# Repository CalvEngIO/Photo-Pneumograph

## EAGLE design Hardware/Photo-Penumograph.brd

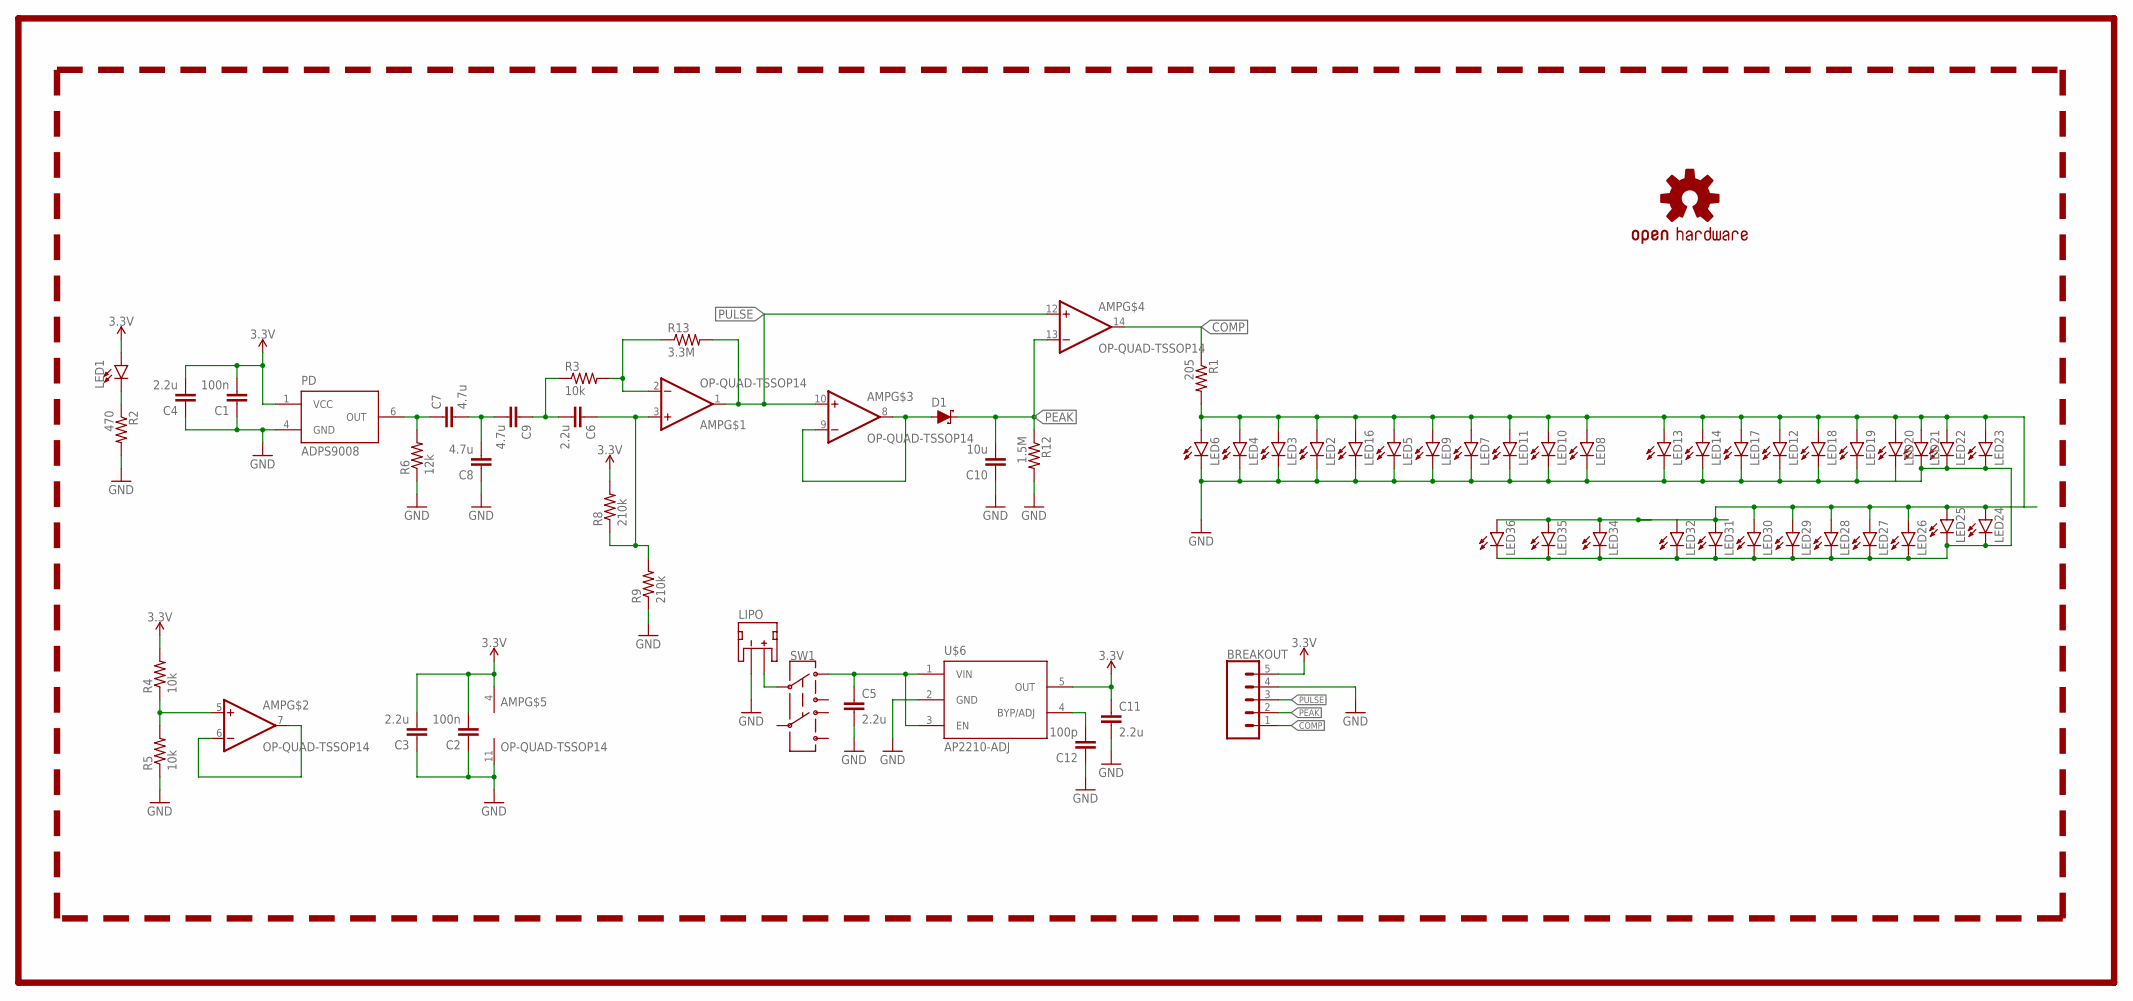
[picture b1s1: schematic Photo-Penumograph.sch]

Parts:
AMP: OP-QUAD-TSSOP14; TSSOP14
BREAKOUT: CONN_05; 1X05
C1, C2: 100n; C0402
C3, C4, C5, C6, C11: 2.2u; C0603
C7, C8, C9: 4.7u; C0603
C10: 10u; C0805
C12: 100p; C0402
D1: SCHOTTKY-SOD-123FL; SOD123
LED1: LEDZ-BEND; 2-SMD.Z-BEND
LED2, LED3, LED4, LED5, LED6, LED7, LED8, LED9, LED10, LED11, LED12, LED13, LED14, LED16, LED17, LED18, LED19, LED20, LED21, LED22, LED23, LED24, LED25, LED26, LED27, LED28, LED29, LED30, LED31, LED32, LED34, LED35, LED36: LED5MM
LIPO: JST_2MM_MALE; JST-2-SMD
LOGO1: OSHW-LOGOS; OSHW-LOGO-S
PD: ADPS9008; 6-PIN.CHIPLED
R1: 205; R0402
R2: 470; R0402
R3, R4, R5: 10k; R0402
R6: 12k; R0402
R8, R9: 210k; R0402
R12: 1.5M; R0402
R13: 3.3M; R0402
SW1: SWITCH.JS202011JCQN; SWITCH.00
U$6: AP2210-ADJ; SOT23-5

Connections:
3.3V: AMP.4 (V+), BREAKOUT.5, C1.2, C2.2, C3.2, C4.2, C11.1, LED1.+ (A), PD.1 (VCC), R4.2, R8.2, U$6.5 (OUT)
ANODE: LED2.A, LED3.A, LED4.A, LED5.A, LED6.A, LED7.A, LED8.A, LED9.A, LED10.A, LED11.A, LED12.A, LED13.A, LED14.A, LED16.A, LED17.A, LED18.A, LED19.A, LED20.A, LED21.A, LED22.A, LED23.A, LED24.A, LED25.A, LED26.A, LED27.A, LED28.A, LED29.A, LED30.A, LED32.A, LED34.A, LED35.A, LED36.A, R1.2
COMP: AMP.14 (OUT), BREAKOUT.1, R1.1
GND: AMP.11 (V-), BREAKOUT.4, C1.1, C2.1, C3.1, C4.1, C5.2, C8.1, C10.1, C11.2, C12.1, LED2.K (C), LED3.K (C), LED4.K (C), LED5.K (C), LED6.K (C), LED7.K (C), LED8.K (C), LED9.K (C), LED10.K (C), LED11.K (C), LED12.K (C), LED13.K (C), LED14.K (C), LED16.K (C), LED17.K (C), LED18.K (C), LED19.K (C), LED20.K (C), LED21.K (C), LED22.K (C), LED23.K (C), LED24.K (C), LED25.K (C), LED26.K (C), LED27.K (C), LED28.K (C), LED29.K (C), LED30.K (C), LED31.K (C), LED32.K (C), LED34.K (C), LED35.K (C), LED36.K (C), LIPO.1 (-), PD.4 (GND), R2.2, R5.1, R6.1, R9.1, R12.2, U$6.2 (GND)
unnamed: AMP.5 (+IN), R4.1, R5.2
unnamed: AMP.6 (-IN), AMP.7 (OUT)
unnamed: C12.2, U$6.4 (BYP/ADJ)
unnamed: LIPO.2 (+), SW1.2
unnamed: C5.1, SW1.1, U$6.1 (VIN), U$6.3 (EN)
unnamed: LED1.- (C), R2.1
unnamed: AMP.8 (OUT), AMP.9 (-IN), D1.ANODE (A)
unnamed: C7.2, C8.2, C9.2
unnamed: C6.2, C9.1, R3.1
unnamed: AMP.2 (-IN), R3.2, R13.1
unnamed: AMP.3 (+IN), C6.1, R8.1, R9.2
unnamed: C7.1, PD.6 (OUT), R6.2
PEAK: AMP.13 (-IN), BREAKOUT.2, C10.2, D1.CATH (C), R12.1
PULSE: AMP.1 (OUT), AMP.10 (+IN), AMP.12 (+IN), BREAKOUT.3, R13.2

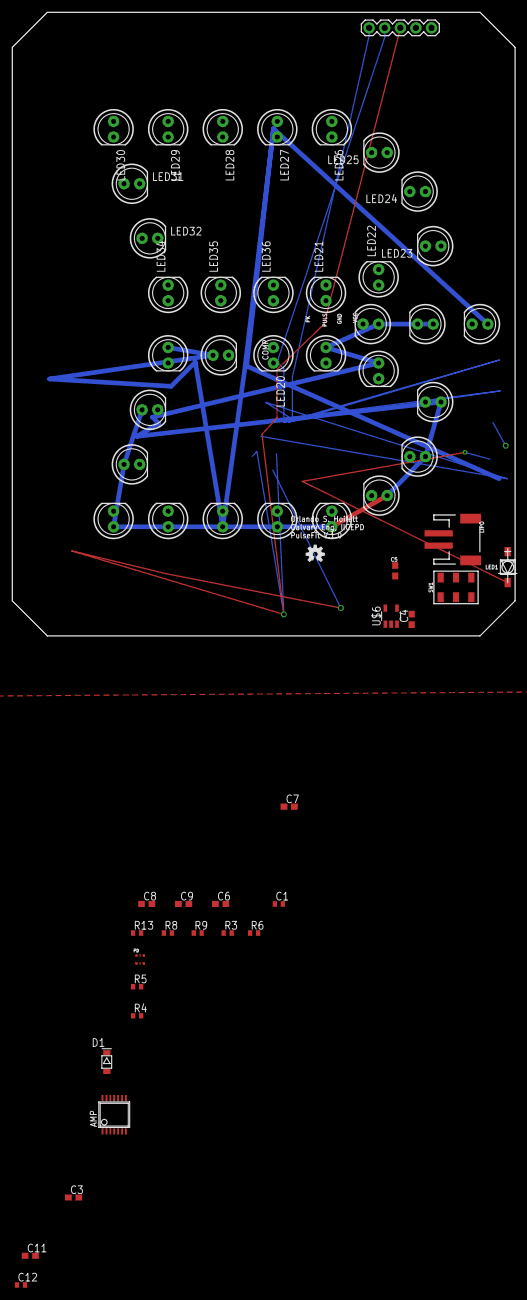
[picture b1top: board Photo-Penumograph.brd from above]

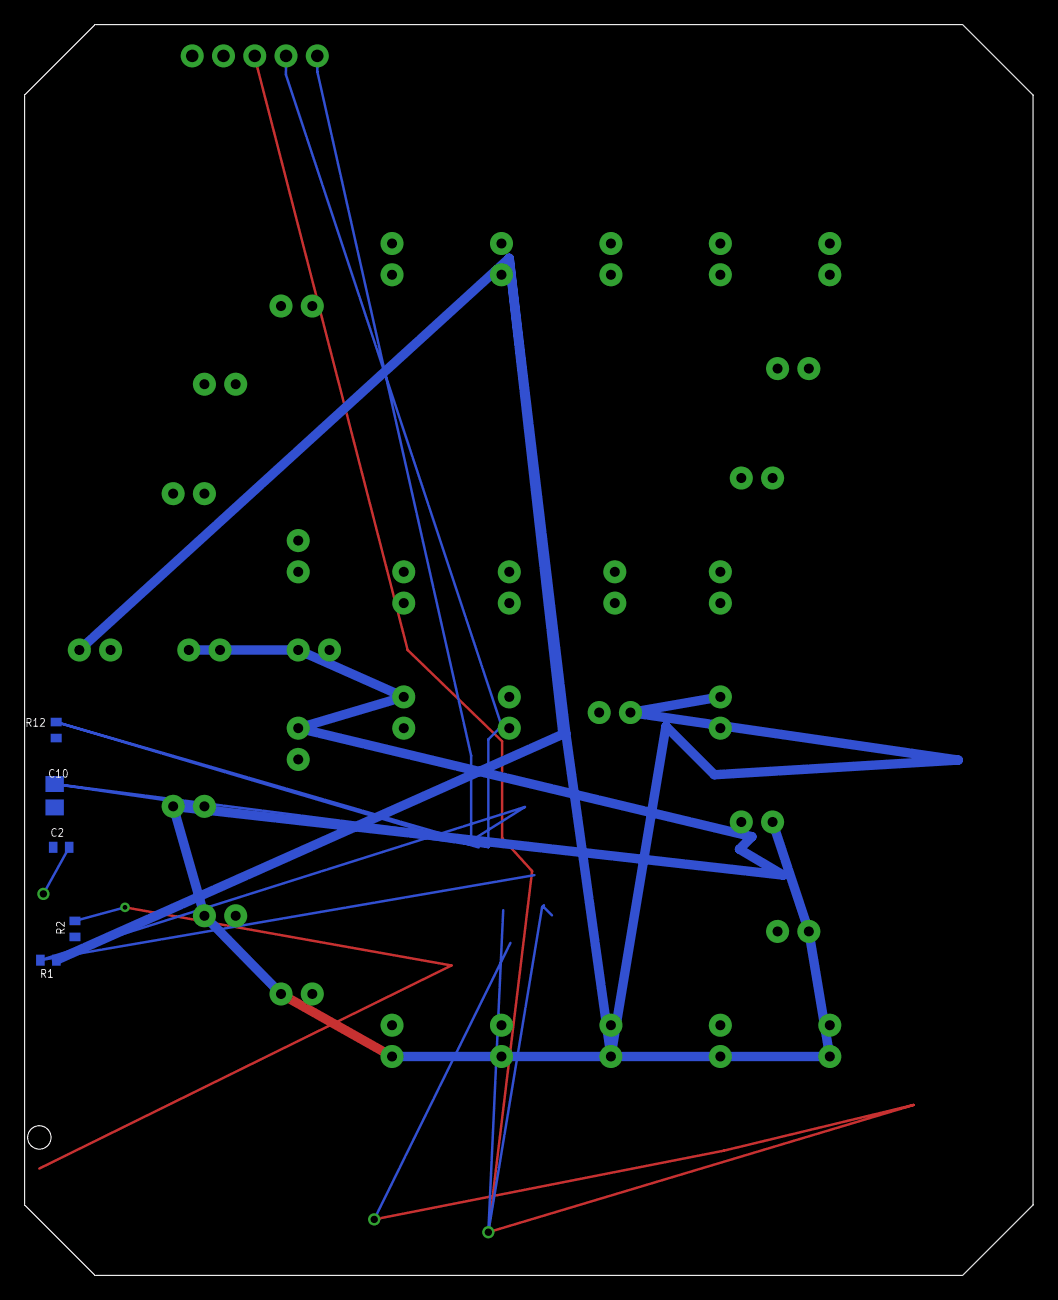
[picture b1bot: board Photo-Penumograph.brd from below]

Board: 2 copper layers, 81.9 x 101.6 mm, 64 parts (5 on the bottom side), 18 nets.

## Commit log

2017-06-07 initial commit lots to do
2017-06-08 Inital lung idea, doesn't expand with breath.
2017-06-09 Improved basic lung design

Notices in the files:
Hardware/Photo-Penumograph.sch:
Creative Commons License
parts and their libraries:
SparkFun-LED: Licensing: Creative Commons ShareAlike 4.0 International - https://creativecommons.org/licenses/by-sa/4.0
